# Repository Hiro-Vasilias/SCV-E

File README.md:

# SCV-E [Smart Construction Vehicle - Electric]
Modular vehicle for construction and transport

<<<<<<<<<<<<Contents>>>>>>>>>>>
  
  Documentation PROJ324.docx contains the documentation of the project submitted to the DLE.
  
  Proj324.xlsx contains the Budget costs and summary along with the Gantt chart.
  
  Buggy V2 V17.f3z contains the Design files Fusion 360
  
  Images Proj324 folder contains the images supporting this project.
  
  The rest shown are the programming code as shown in the document appendix

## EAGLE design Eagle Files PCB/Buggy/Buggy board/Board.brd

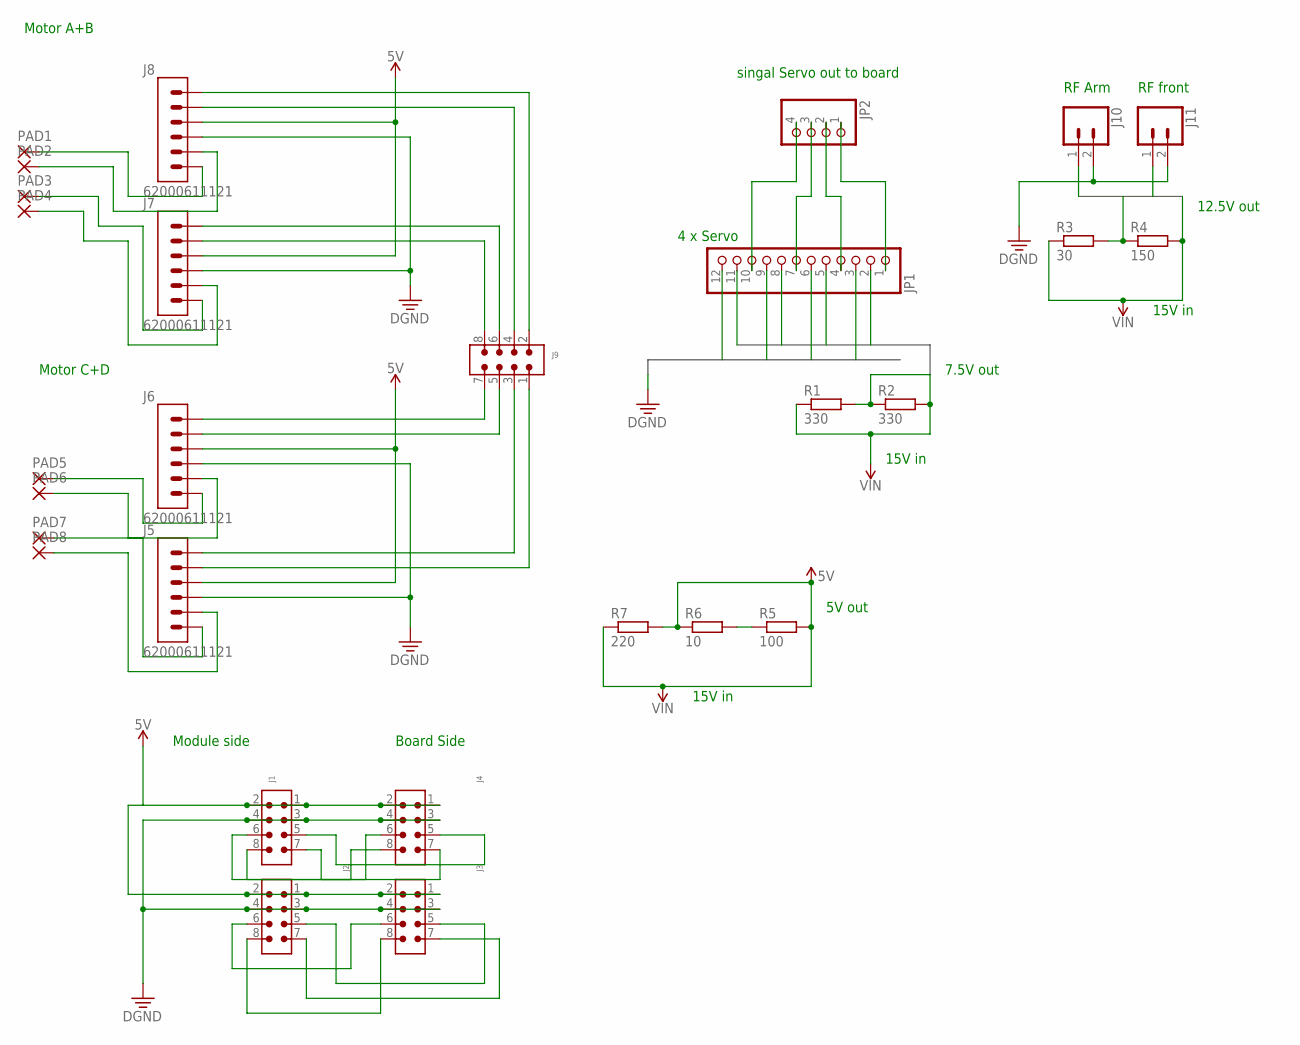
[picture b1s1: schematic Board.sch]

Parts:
J1, J2, J3, J4, J9: 6130XX21021_61300821021; 61300821021
J5, J6, J7, J8: 62000611121
J10, J11: CONN_02LOCK_LONGPADS; 1X02_LOCK_LONGPADS
JP1: PINHD-1X12; 1X12
JP2: PINHD-1X4/90; 1X04/90
PAD1, PAD2, PAD3, PAD4, PAD5, PAD6, PAD7, PAD8: 3,17/1,3
R1, R2: 330; 0207/10
R3: 30; 0207/10
R4: 150; 0207/10
R5: 100; 0207/10
R6: 10; 0207/10
R7: 220; 0207/10

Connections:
5V: J1.1, J1.2, J2.1, J2.2, J3.1, J3.2, J4.1, J4.2, J5.3, J6.3, J7.3, J8.3
B$1: JP1.3, JP1.6, JP1.9, JP1.12
B$2: JP1.2, JP1.5, JP1.8, JP1.11, R1.1, R1.2, R2.1, R2.2
B$3: J10.1, J11.1, R3.1, R3.2, R4.1, R4.2
DGND: J1.3, J1.4, J2.3, J2.4, J3.3, J3.4, J4.3, J4.4, J5.4, J6.4, J7.4, J8.4, J10.2, J11.2
unnamed: J1.8, J4.8
unnamed: J1.6, J4.6
unnamed: J1.7, J4.7
unnamed: J2.5, J3.5
unnamed: J1.5, J4.5
unnamed: J2.7, J3.7
unnamed: J2.8, J3.8
unnamed: J2.6, J3.6
unnamed: J6.6, PAD5.1
unnamed: J5.6, PAD7.1
unnamed: J6.5, PAD6.1
unnamed: J5.5, PAD8.1
unnamed: J8.6, PAD1.1
unnamed: J8.5, PAD2.1
unnamed: J7.6, PAD3.1
unnamed: J7.5, PAD4.1
unnamed: J5.2, J9.1
unnamed: J5.1, J9.3
unnamed: J6.2, J9.5
unnamed: J6.1, J9.7
unnamed: J7.2, J9.8
unnamed: J7.1, J9.6
unnamed: J8.2, J9.4
unnamed: J8.1, J9.2
unnamed: JP1.1, JP2.1
unnamed: JP1.4, JP2.2
unnamed: JP1.7, JP2.3
unnamed: JP1.10, JP2.4
unnamed: R5.1, R6.2
VIN: R5.2, R6.1, R7.1, R7.2

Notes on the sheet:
Module side
Board Side
Motor A+B
Motor C+D
15V in
7.5V out
4 x Servo
singal Servo out to board
RF front
RF Arm
12.5V out
5V out

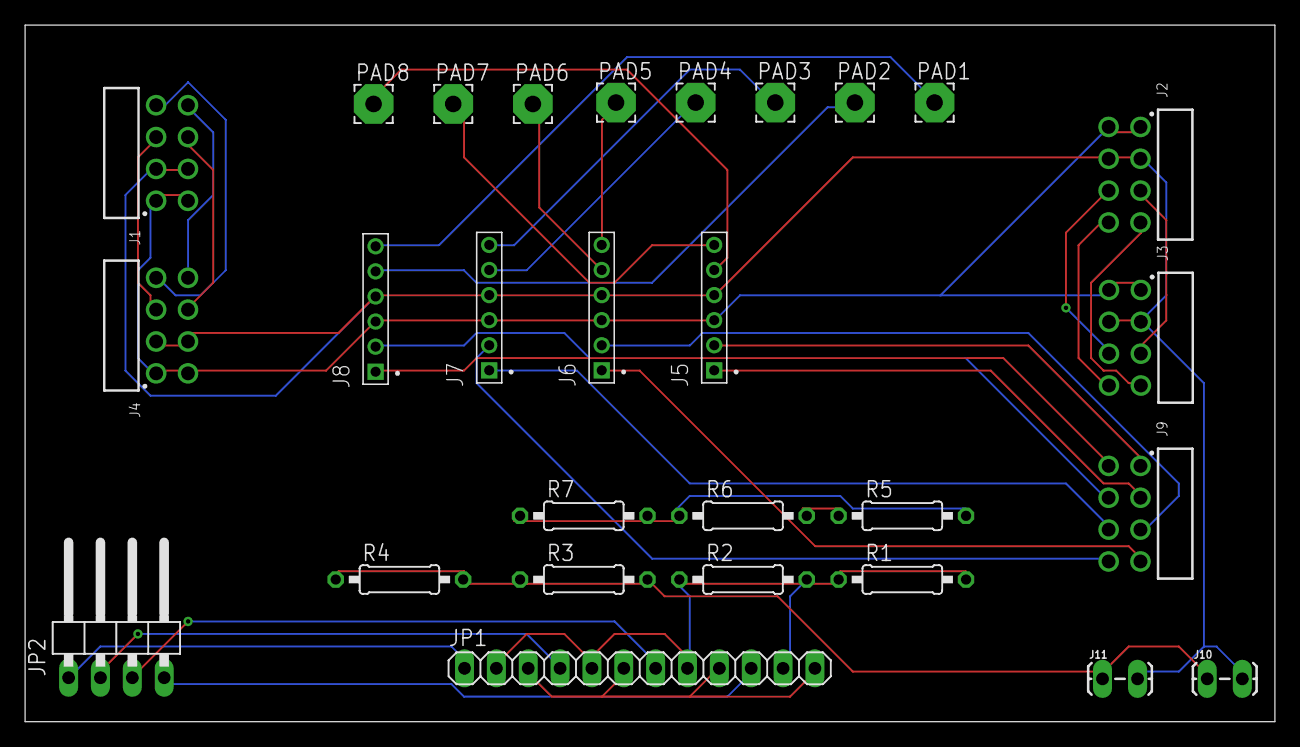
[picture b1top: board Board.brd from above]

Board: 2 copper layers, 99.7 x 55.5 mm, 28 parts (0 on the bottom side), 35 nets.

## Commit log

2021-12-09 Final Code to SCV-E
    Use with Platform IO on VS code
2021-12-09 Create images
2021-12-16 Add files via upload
    Uploaded for the Extended Deadline.
    Please mark this one

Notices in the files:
parts and their libraries:
Wurth_Connectors_WR-PHD: Copyright: Würth Elektronik
SparkFun-Connectors: Licensing: Creative Commons ShareAlike 4.0 International - https://creativecommons.org/licenses/by-sa/4.0
